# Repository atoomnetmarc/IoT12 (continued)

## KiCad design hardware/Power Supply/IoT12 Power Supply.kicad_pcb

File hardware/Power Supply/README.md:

This Power Supply PCB powers the IoT12 Control Board. It features a relay that can be activated by the Control Board to provide 24V power to the soldering iron. However, the relay can only be activated when the user switch on J2 is closed. This enables the user to power down the heating of the soldering iron independent of what the Control Board is able to, which is a nice feature of an internet connected soldering station.

# Warning

If you choose to replicate and use this PCB you are doing so on your own risk. It is very much possible to set your house on fire when something goes wrong or die when touching the wrong spots on the PCB.

When handling this PCB you are working with dangerous mains voltage ⚡. When touched it hurts the entire time you are dying ☠️. The bottom and top the PCB contain exposed tracks and screw terminals carry deadly mains voltage.

In conclusion, do not use this PCB.

# Assembly instructions Power Supply

Use the [interactive BOM](bom/ibom.html) to identify values and positions of the components.

Solder every SMD component. Begin with the smallest, end with the tallest.

Solder every through hole component. Begin with the smallest, end with the tallest However, do not solder the Mean Well power supply (PS1) module itself yet.

Clean the PCB.

You have now something that looks like this:

Connect current limited (100mA) 24V on the outputs of where PS1 should be. Possibly you could connect the right leg of F1 to 24V. Current should be under 10mA. Now D4 should light up. Measure the 5V pin, it should measure about 5.2V.
Connect a jumper to J2. Connect 3V3 to gnd and the '+24V ON'-pin of J3. D5 should light up and you hear a relay click. Current increases to about 20mA.

All went well? Disconnect 24V and solder PS1.

Measure 1M between GND on J3 and Earth on J1. Measure no connection between GND on J3 and L and N on J1.

Place bottom of PCB on isolating material.

Connect leads of an unconnected grounded mains cable to J1. Use the correct screw terminal for the correct mains line. If top of PCB is not clear enough, use labels on bottom of PCB and/or consult the PCB design files.

Connect multimeter to right leg of F1 and GND to measure voltage.

⚡ Connect the mains cable to the wall socket.

LED D4 should light up again. Look, no touch, at multimeter. It should read 24V.

Disconnect the mains cable from the wall socket. Disconnect multimeter. Notice D4 is still lit. It will stop emitting light after some unit of time. The capacitors in the Mean Well power supply still contain some charge and are discharging slowly.

# Done

Done!

# Pinout J1, high voltage side

AC power input.

| Pin # | Description                                       |
| ----- | ------------------------------------------------- |
| 1     | Earth, connected with 990KΩ resistor array to GND |
| 2     | AC line                                           |
| 3     | AC neutral                                        |

# Pinout J2, 24v interlock switch

In series with 24V_ON so the user can override when soldering iron heater receives power.

| Pin # | Description |
| ----- | ----------- |
| 1     | 24V_ON      |
| 2     | 24V_ON      |

# Pinout J3, Board-to-board

Goes to control board.

| Pin # | Description        |
| ----- | ------------------ |
| 1     | 24V switched power |
| 2     | 5V always on       |
| 3     | GND                |
| 4     | 24V_ON             |

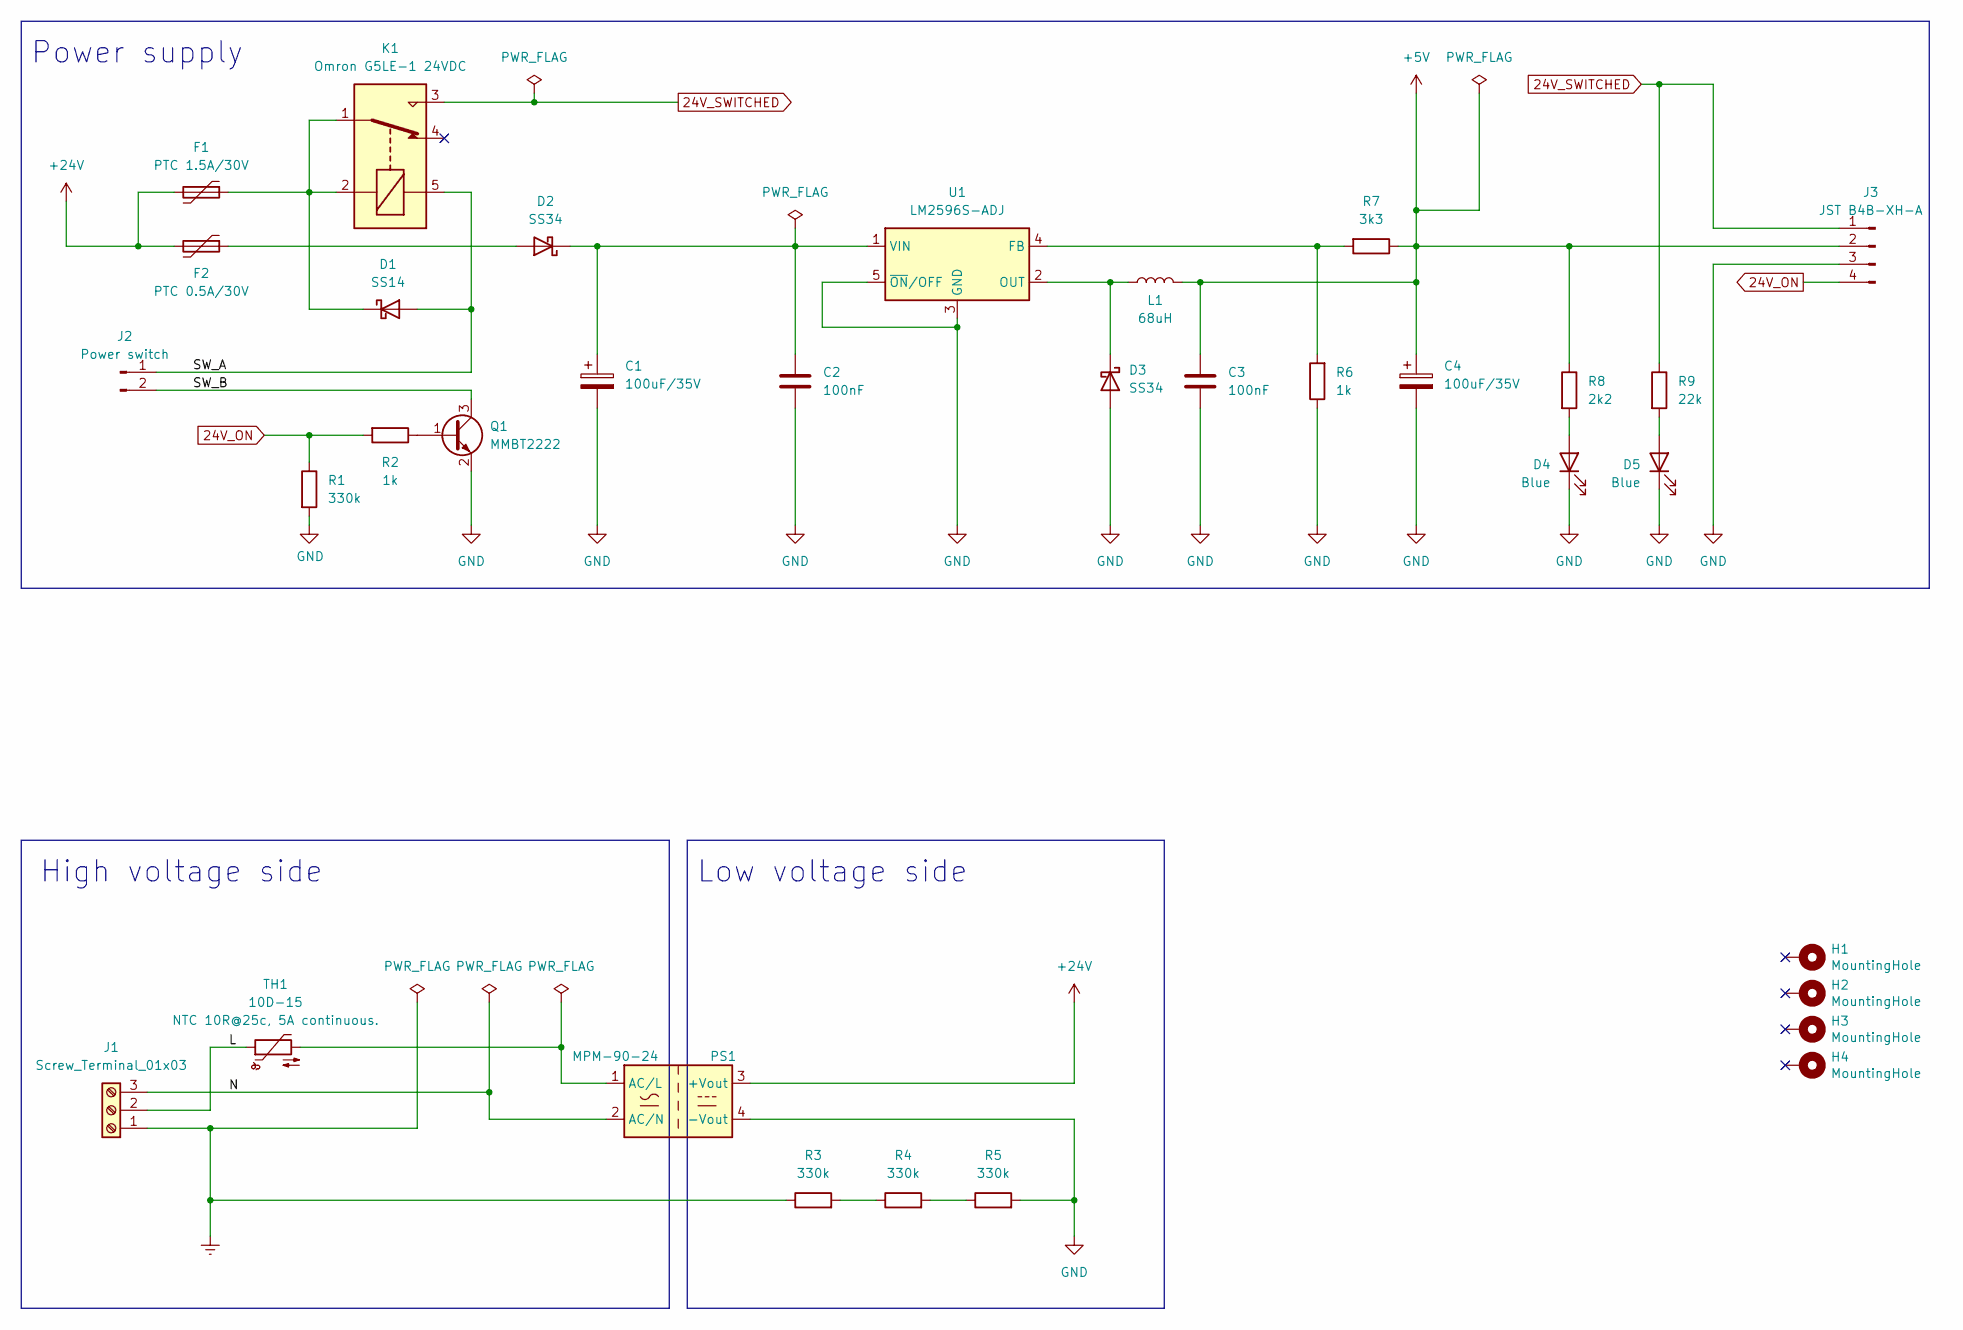
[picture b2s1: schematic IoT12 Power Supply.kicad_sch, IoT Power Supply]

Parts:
C1, C4: 100uF/35V; CP_Elec_6.3x7.7
C2, C3: 100nF; C_0805_2012Metric_Pad1.18x1.45mm_HandSolder
D1: SS14; D_SMA
D2, D3: SS34; D_SMA
D4, D5: Blue; LED_0805_2012Metric_Pad1.15x1.40mm_HandSolder
F1: PTC 1.5A/30V; RV_Disc_D9mm_W3.3mm_P5mm
F2: PTC 0.5A/30V; RV_Disc_D7mm_W3.4mm_P5mm
H1, H2, H3, H4: MountingHole; MountingHole_3.2mm_M3_Pad_Via
J1: Screw_Terminal_01x03; TerminalBlock_Weidmueller-PM-5.08-03-90-3.5SN-BK-BX
J2: JST B2B-XH-A; JST_XH_B2B-XH-A_1x02_P2.50mm_Vertical
J3: JST B4B-XH-A; JST_XH_B4B-XH-A_1x04_P2.50mm_Vertical
K1: Omron G5LE-1 24VDC; Relay_SPDT_Omron-G5LE-1
L1: 68uH; L_12x12mm_H8mm
PS1: MPM-90-24; Converter_ACDC_MeanWell_MPM-90-xx_THT
Q1: MMBT2222; SOT-23
R1, R3, R4, R5: 330k; R_0805_2012Metric_Pad1.20x1.40mm_HandSolder
R2, R6: 1k; R_0805_2012Metric_Pad1.20x1.40mm_HandSolder
R7: 3k3; R_0805_2012Metric_Pad1.20x1.40mm_HandSolder
R8: 2k2; R_0805_2012Metric_Pad1.20x1.40mm_HandSolder
R9: 22k; R_0805_2012Metric_Pad1.20x1.40mm_HandSolder
TH1: 10D-15; RV_Disc_D15.5mm_W4.5mm_P7.5mm
U1: LM2596S-ADJ; TO-263-5_TabPin3

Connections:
24V_ON: J3.4, R1.1, R2.2
24V_SWITCHED: J3.1, K1.3, R9.1
+5V: C3.1, C4.1, J3.2, L1.2, R7.1, R8.1
+24V: F1.2, F2.2, PS1.3 (+Vout)
/L: J1.2, TH1.1
/N: J1.3, PS1.2 (AC/N)
/SW_A: D1.2 (A), J2.1, K1.5
/SW_B: J2.2, Q1.3 (C)
Earth: J1.1, R3.1
GND: C1.2, C2.2, C3.2, C4.2, D3.2 (A), D4.1 (K), D5.1 (K), J3.3, PS1.4 (-Vout), Q1.2 (E), R1.2, R5.2, R6.1, U1.3 (GND), U1.5 (~ON/OFF)
unnamed: D1.1 (K), F1.1, K1.1, K1.2
unnamed: D2.2 (A), F2.1
unnamed: C1.1, C2.1, D2.1 (K), U1.1 (VIN)
unnamed: D3.1 (K), L1.1, U1.2 (OUT)
unnamed: D4.2 (A), R8.2
unnamed: D5.2 (A), R9.2
unnamed: PS1.1 (AC/L), TH1.2
unnamed: Q1.1 (B), R2.1
unnamed: R3.2, R4.1
unnamed: R4.2, R5.1
unnamed: R6.2, R7.2, U1.4 (FB)

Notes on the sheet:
Low voltage side
Power supply
High voltage side

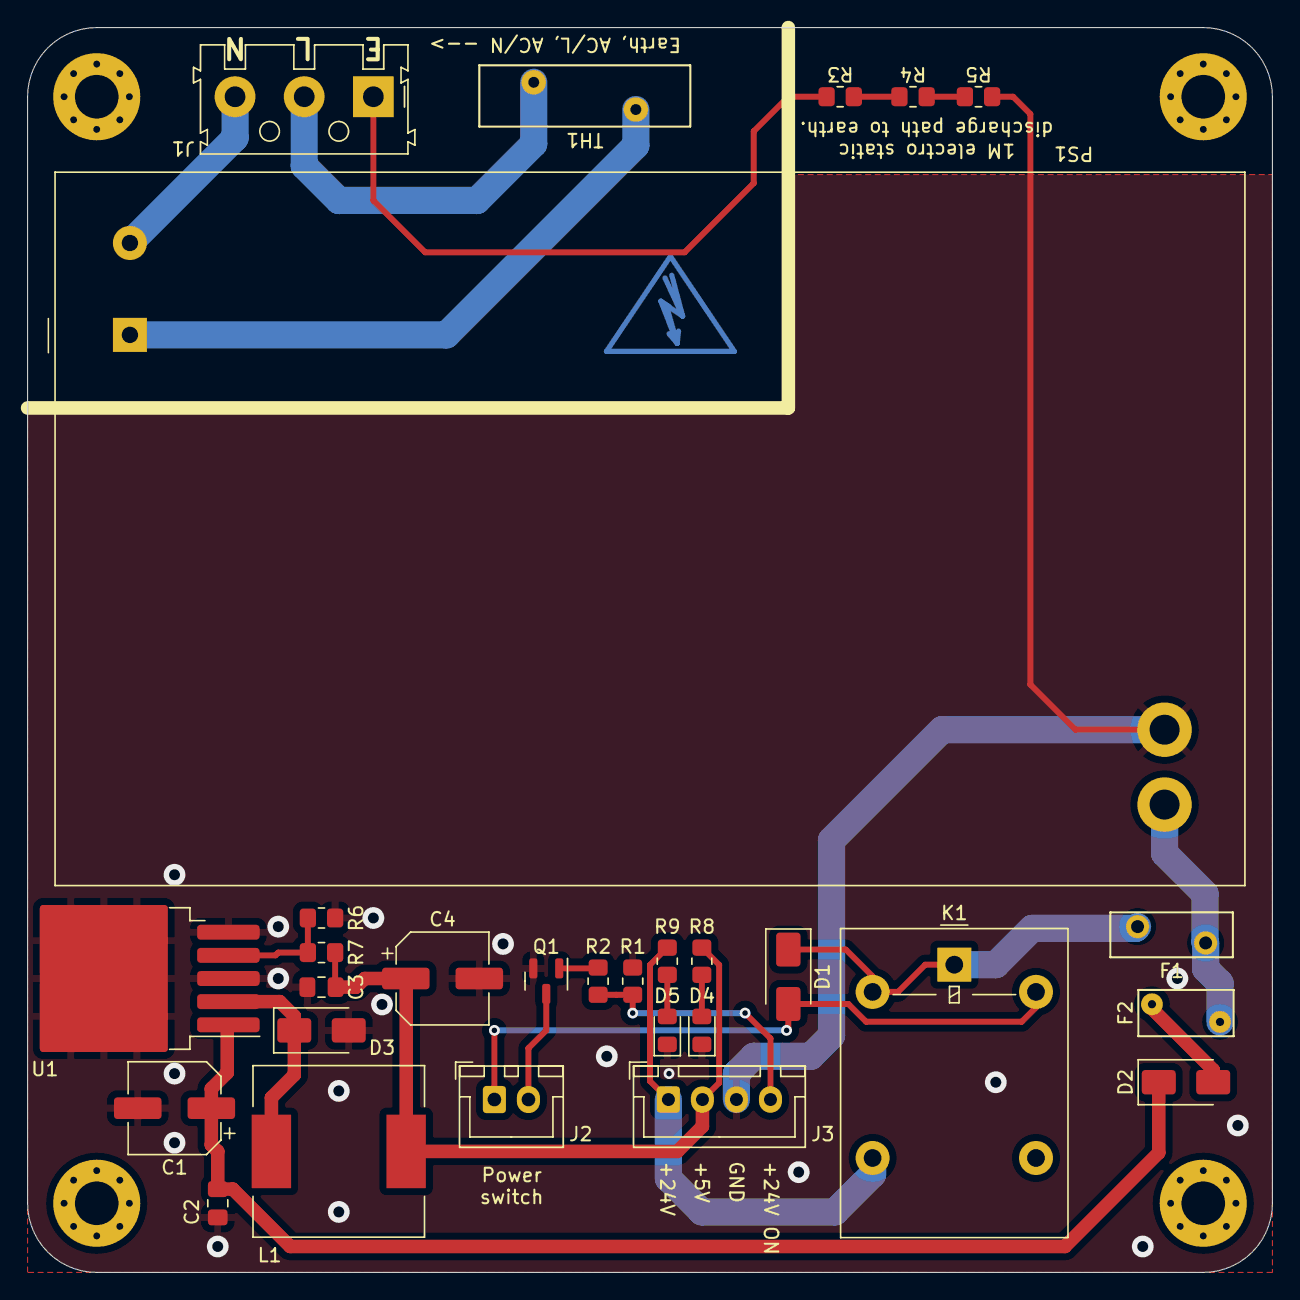
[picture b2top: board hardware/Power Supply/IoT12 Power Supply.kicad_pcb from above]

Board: 2 copper layers, 91.4 x 91.4 mm, 33 parts (0 on the bottom side), 21 nets.

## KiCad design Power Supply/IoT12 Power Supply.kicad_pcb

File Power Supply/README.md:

# Warning

If you choose to replicate and use this PCB you are doing so on your own risk. It is very much possible to set your house on fire when something goes wrong or die when touching the wrong spots on the PCB.

When handling this PCB you are working with dangerous mains voltage ⚡. When touched it hurts the entire time you are dying ☠️. The bottom and top the PCB contain exposed tracks and screw terminals carrying deadly mains voltage.

In conclusion, do not use this PCB. Power the IoT12 control board with some other safe and certified power supply.

# Assembly instructions Power Supply

## Solder

Solder components in the following order.
Use the [interactive BOM](bom/ibom.html) for values and positions of the components.

### Resistor

R2.

### Diode

D2.

### Screw terminal

J1, J2.

### Power supply

One off PS1, PS2 or PS3.

## Testing

Place bottom of PCB on isolating material.

Connect leads of a mains cable to J1. Use the correct screw terminal for the correct mains line. If top of PCB is not clear enough, use labels on bottom of PCB and/or consult the PCB design files.

⚡ Connect the mains cable to the wall socket.

Notice the green LED lighting up. Now carefully measure the low voltage side on screw terminal J2. You should measure 24V volts (if you mounted a Mean Well MPM-90-24).

Disconnect the mains cable from the wall socket. Notice that the green LED is still lit. It will stop emitting light after some unit of time. The capacitors in the Mean Well power supply still contain some chare and are discharging slowly.

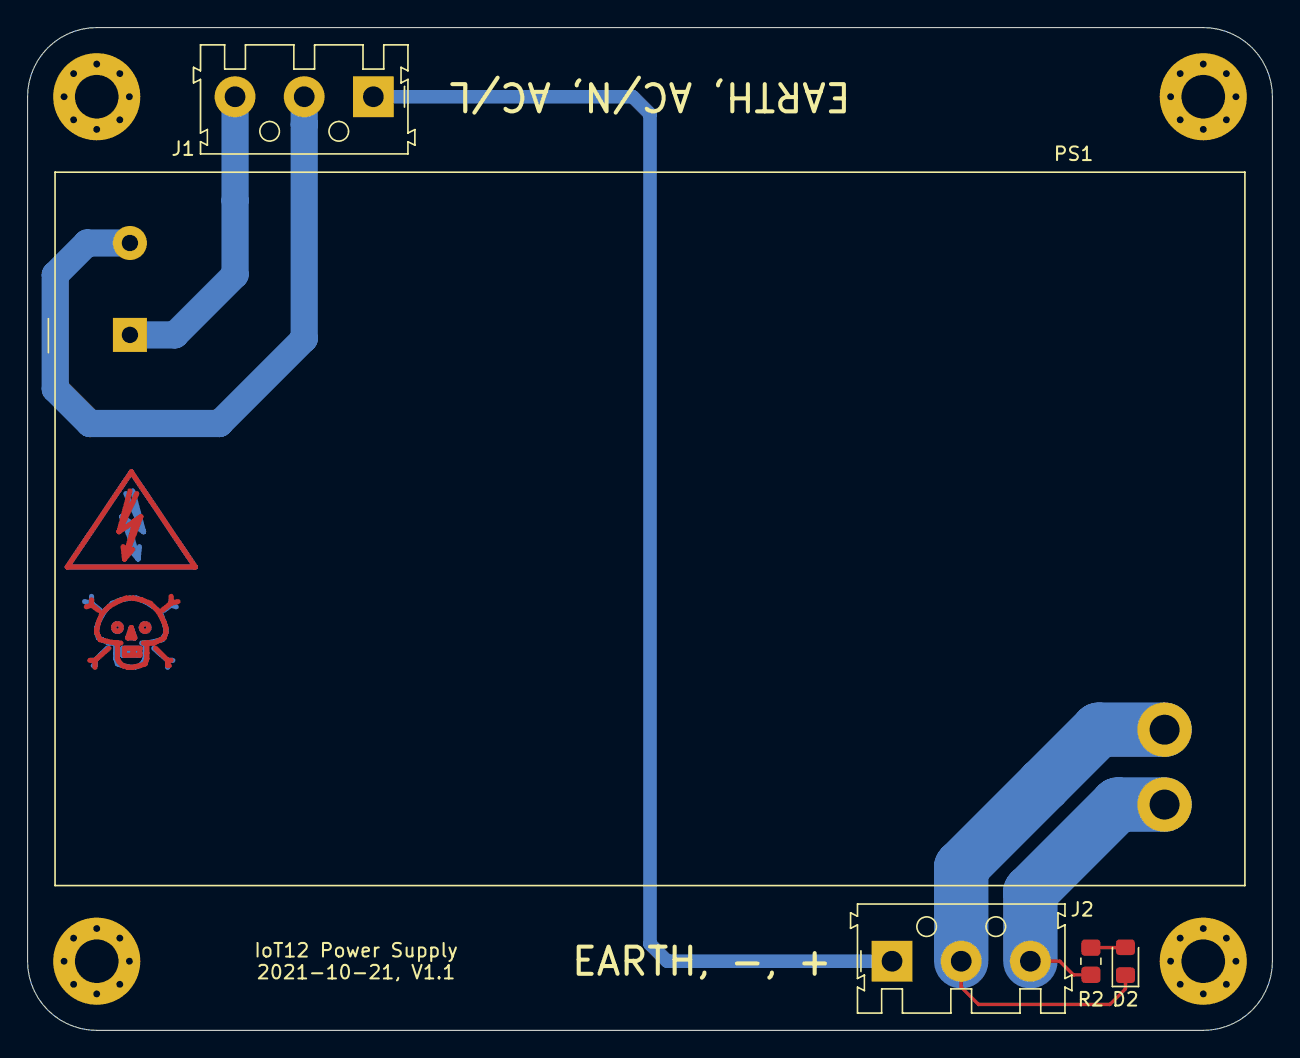
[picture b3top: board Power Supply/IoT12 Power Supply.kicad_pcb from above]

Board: 2 copper layers, 91.4 x 73.7 mm, 9 parts (0 on the bottom side), 6 nets.

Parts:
D2: Green; LED_0805_2012Metric_Pad1.15x1.40mm_HandSolder
H1, H2, H3, H4: MountingHole; MountingHole_3.2mm_M3_Pad_Via
J1, J2: Screw_Terminal_01x03; TerminalBlock_Weidmueller-PM-5.08-03-90-3.5SN-BK-BX
PS1: MPM-90-24; Converter_ACDC_MeanWell_MPM-90-xx_THT
R2: 4K7; R_0805_2012Metric_Pad1.20x1.40mm_HandSolder

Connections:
/L: J1.3, PS1.1
/N: J1.2, PS1.2
/Vout+: J2.3, PS1.3, R2.1
/Vout-: D2.1, J2.2, PS1.4
Earth: J1.1, J2.1
unnamed: D2.2, R2.2

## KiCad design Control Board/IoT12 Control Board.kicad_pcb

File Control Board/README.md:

# Assembly instructions Control Board

## Solder

Solder components in the following order.
Use the [interactive BOM](bom/ibom.html) for values and positions of the components.

### Integrated circuit

U1.
U2.
U3, U4.
U5.
U6.
U7.

### Transistor

Q1, Q2.
Q3.

### Diode

D1, D2, D3, D4, D12.
D5.
D6, D7, D8.
D9.
D10.
D11.

### Inductor

L1.
L2.

### Resistor

R1.
R10, R11, R12.
R20.
R21.
R30.
R31, R32, R33, R34.
R40.
R52.
R50, R51, R53, R54, R55, R56, R57, R58, R59, R82.
R60, R61, R62, R63. **Read schematic notes about these resistors.**
R64.
R70.
R71, R72.
R80, R81, R83, R84.

### Capacitor

C1, C2.
C10.
C20, C21, C22.
C30, C31, C32, C33, C34, C35, C36, C37, C38.
C40, C41.
C50, C60, C61.
C70, C71, C73.

### Crystal

Y1.

## Clean PCB

[Clean your printed circuit board](http://letmegooglethat.com/?q=how+to+clean+flux+after+soldering). It should be squeaky clean, no flux residue or other crud should remain.

### Switch, back of PCB

SW2.

### Connector, back of PCB

J10.

### Connector, front of PCB

A2: 2 pcs of 1x8pin 2.54mm female headers.

### Connector, back of PCB

A1: 2 pcs of 1x19pin 2.54mm female headers.
J9, J10. 2x5pin 2.54mm male headers.

### Fuse, back of PCB

## Clean PCB, again.

Yes, do it.

### Encoder, front of PCB

Solder SW1 and remove nut and washer.

### Module, front of PCB

A3. Use pin male headers. Also for SPK pins.

## Inspect

Inspect all solder joints. They should all be [nicely soldered](https://www.google.com/search?q=proper+solder+joint), no [solder bridges](https://www.google.com/search?q=picture+of+a+solder+bridge) should be present. Have a magnifying glass or (digital) microscope? Use it.

### GX12-5 connector

Solder some wires between a GX12-5 socket connector and the back of the pcb. On the back of the pcb there are a few pads labeled 1 to 5, solder them to pin 1 to 5 on the GX12-5 connector.

| Pin#  | Wire color    | Description   |
| --:   | --            | --            |
| 1     | blue          | shake         |
| 2     | white         | NTC           |
| 3     | green         | ESD           |
| 4     | black         | T12-          |
| 5     | red           | T12+          |

## Testing

Connect a (KSGER) T12 solder iron handle with the T12 tip firmly seated inside.

- Measure about 1MΩ between the tip of the iron and EARTH hole at the Power supply connection on the PCB.
- Now measure some values at the solder iron connector holes.\
The heater resistor between 4 (black) and 5 (red): 8Ω
- Switch over to measure mV. When you have not touched the handle and tip for half an hour you should read 0mV. Grab the tip with your hand. You should notice an increasing voltage, possibly a rise until 0.1mV. It is possible your voltmeter is not capable of measuring in the microvolt range. You can heat the tip with a flame for a few seconds to increase the voltage some more.
- The NTC between 4 (black) and 2 (white): 5KΩ@22°C, but that could vary slightly when not measuring at the same room temperature.
- Test the tilt sensor. Point iron up and measure between 1 (blue) and 3 (green): >2MΩ\
Point iron down and measure a low resistance: <100Ω

Solder a red wire to 24V and black wire to GND of the power supply connector holes, both on the back.\
Slowly increase power supply until 10V with max 50mA power. Measure voltage at C71. You should measure 5V. The current draw should be under 10mA.

Switch off power supply and mount the LCD display module and the ESP32 module.

Increase maximum power supply current to 250mA. Instantly increase voltage to 5V, the slowly to 10V, current should not exceed 150mA. When at 10V the current draw should be under 100mA.
You may increase voltage to 24V, consumed power should be under 40mA.

When all tests went well, start writing your own firmware. Or [flash my firmware](https://github.com/atoomnetmarc/IoT12-firmware)

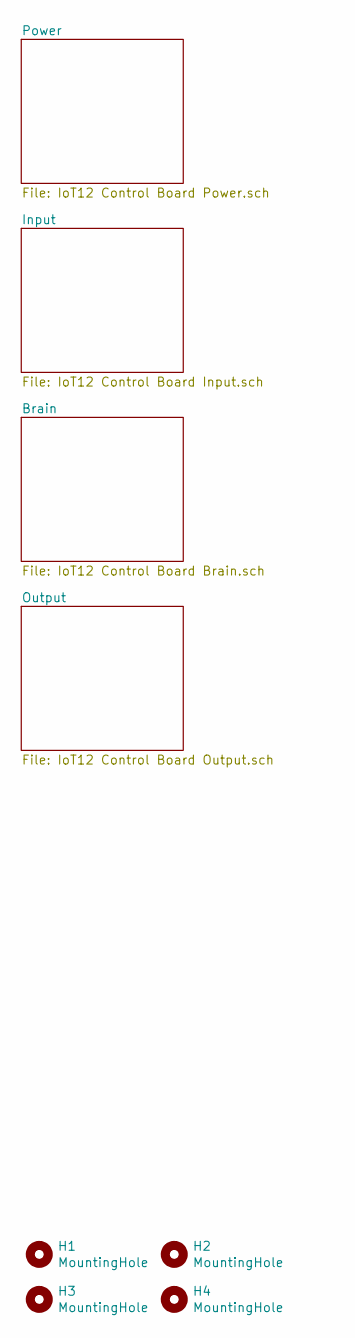
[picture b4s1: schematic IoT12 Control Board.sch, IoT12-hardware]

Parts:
H1, H2, H3, H4: MountingHole; MountingHole_3.2mm_M3_Pad_Via

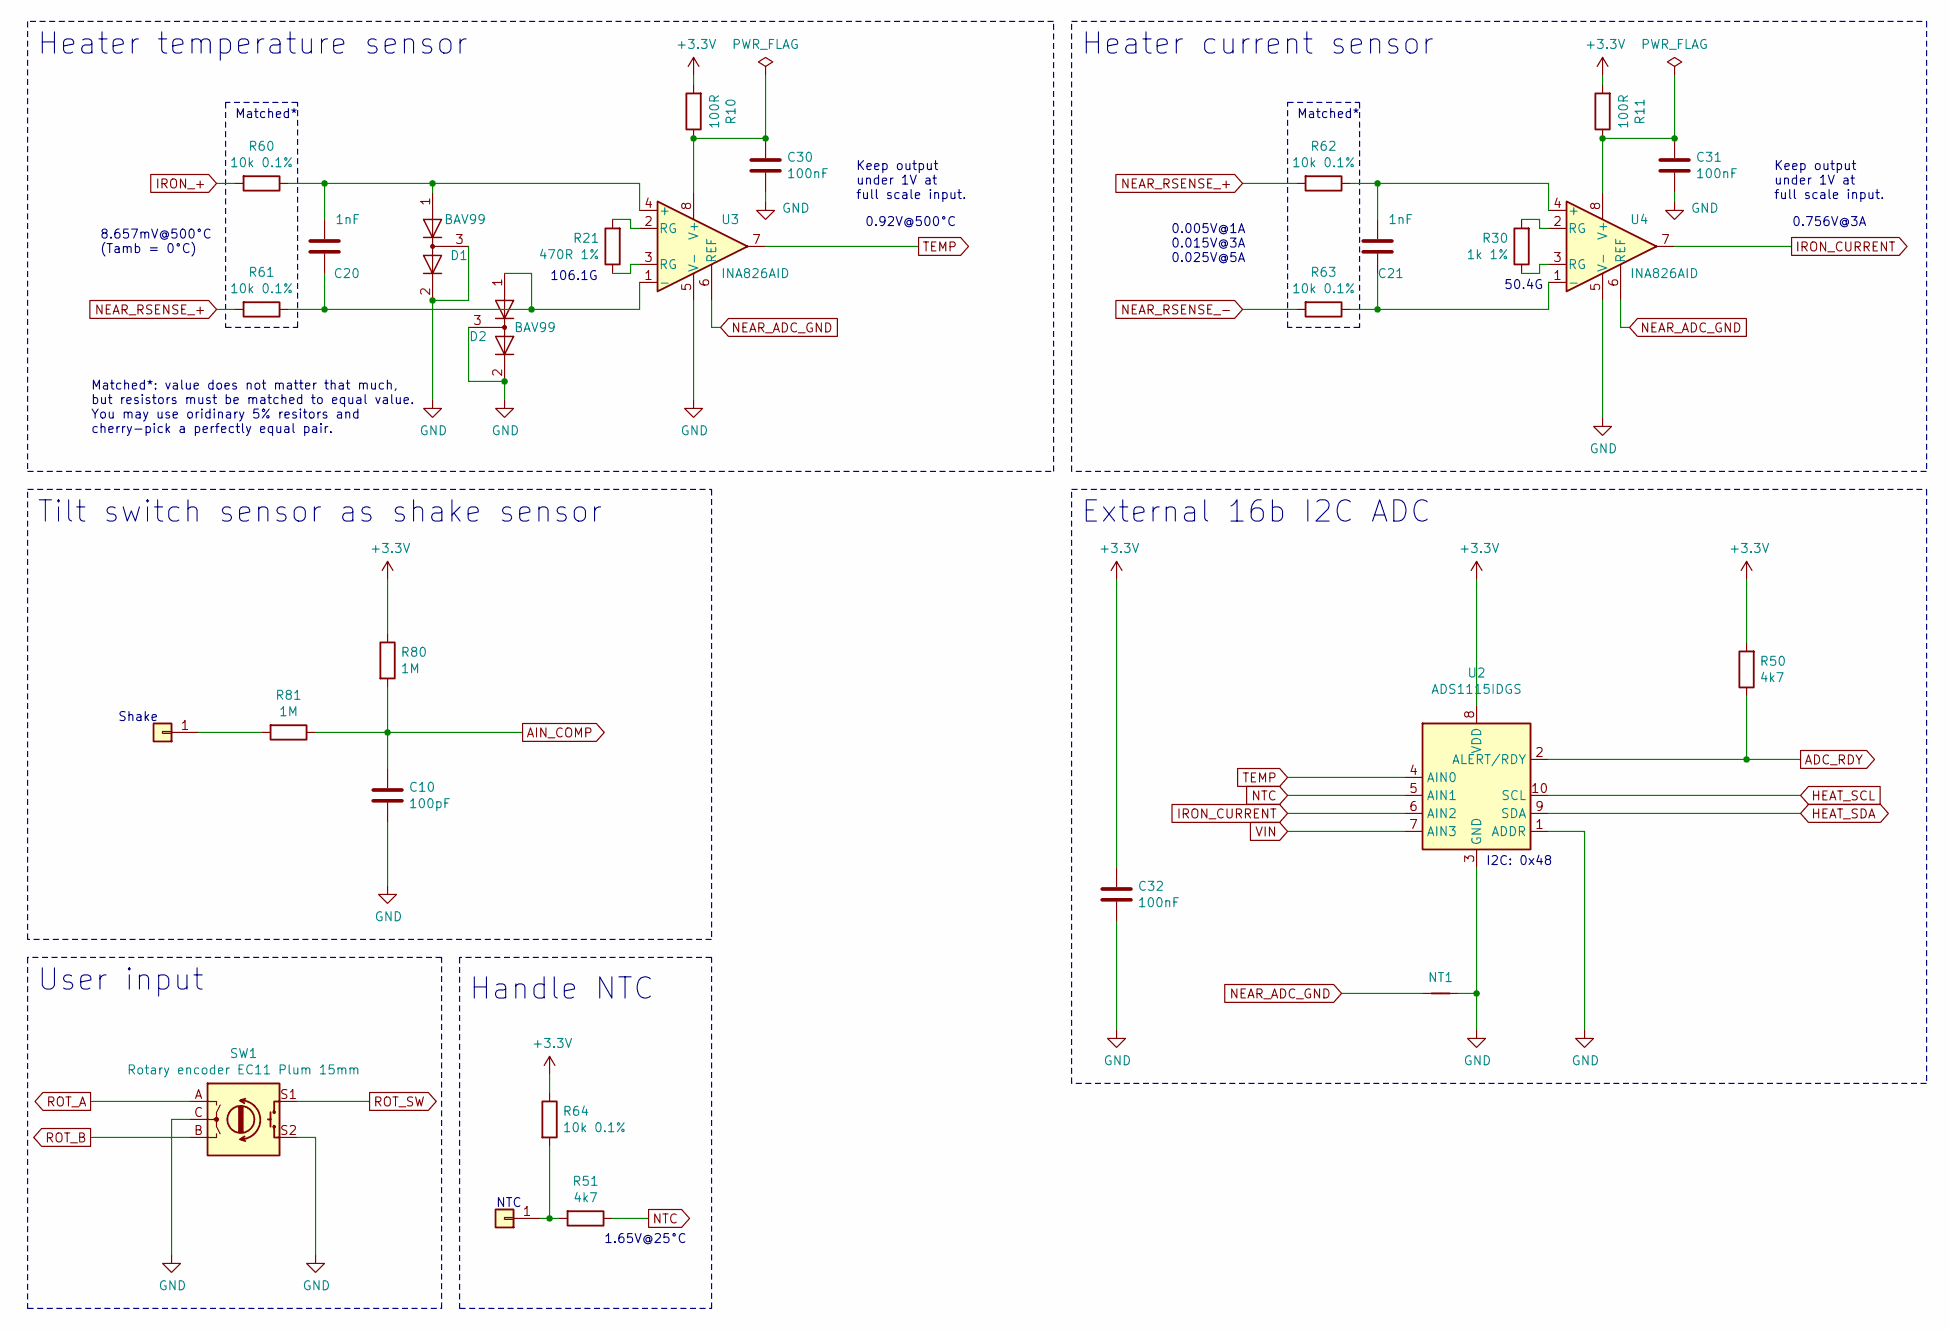
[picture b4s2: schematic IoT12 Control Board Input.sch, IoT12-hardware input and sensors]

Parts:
C10: 100pF; C_0805_2012Metric_Pad1.18x1.45mm_HandSolder
C20, C21: 1nF; C_0805_2012Metric_Pad1.18x1.45mm_HandSolder
C30, C31, C32: 100nF; C_0805_2012Metric_Pad1.18x1.45mm_HandSolder
D1, D2: BAV99; SOT-23
J1, J2: TestPoint_THTPad_D2.0mm_Drill1.0mm
NT1: NetTie-2_SMD_Pad0.25mm
R10, R11: 100R; R_0805_2012Metric_Pad1.20x1.40mm_HandSolder
R21: 470R 1%; R_0805_2012Metric_Pad1.20x1.40mm_HandSolder
R30: 1k 1%; R_0805_2012Metric_Pad1.20x1.40mm_HandSolder
R50, R51: 4k7; R_0805_2012Metric_Pad1.20x1.40mm_HandSolder
R60, R61, R62, R63, R64: 10k 0.1%; R_0805_2012Metric_Pad1.20x1.40mm_HandSolder
R80, R81: 1M; R_0805_2012Metric_Pad1.20x1.40mm_HandSolder
SW1: Rotary encoder EC11 Plum 15mm; RotaryEncoder_Alps_EC11E-Switch_Vertical_H20mm_CircularMoun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
U2: ADS1115IDGS; TSSOP-10_3x3mm_P0.5mm
U3, U4: INA826AID; SOIC-8_3.9x4.9mm_P1.27mm

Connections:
ADC_RDY: R50.1, U2.2 (ALERT/RDY); also elsewhere on the board
AIN_COMP: C10.1, R80.2, R81.1; also elsewhere on the board
GND: C10.2, C30.2, C31.2, C32.2, D1.2 (A), D1.3 (K), D2.2 (A), D2.3 (K), NT1.2, SW1.C, SW1.S2, U2.1 (ADDR), U2.3 (GND), U3.5 (V-), U4.5 (V-); also elsewhere on the board
HEAT_SCL: U2.10 (SCL); also elsewhere on the board
HEAT_SDA: U2.9 (SDA); also elsewhere on the board
IRON_+: R60.2; also elsewhere on the board
IRON_CURRENT: U2.6 (AIN2), U4.7; also elsewhere on the board
NEAR_ADC_GND: NT1.1, U3.6 (REF), U4.6 (REF)
NEAR_RSENSE_+: R61.2, R62.2; also elsewhere on the board
NEAR_RSENSE_-: R63.2; also elsewhere on the board
NTC: R51.1, U2.5 (AIN1); also elsewhere on the board
unnamed: C20.1, D1.1 (K), R60.1, U3.4 (+)
unnamed: C20.2, D2.1 (K), R61.1, U3.1 (-)
unnamed: C21.1, R62.1, U4.4 (+)
unnamed: C21.2, R63.1, U4.1 (-)
unnamed: C30.1, R10.1, U3.8 (V+)
unnamed: C31.1, R11.1, U4.8 (V+)
unnamed: J1.1, R81.2
unnamed: J2.1, R51.2, R64.2
unnamed: R21.1, U3.3 (RG)
unnamed: R21.2, U3.2 (RG)
unnamed: R30.1, U4.3 (RG)
unnamed: R30.2, U4.2 (RG)
ROT_A: SW1.A; also elsewhere on the board
ROT_B: SW1.B; also elsewhere on the board
ROT_SW: SW1.S1; also elsewhere on the board
TEMP: U2.4 (AIN0), U3.7; also elsewhere on the board
VIN: U2.7 (AIN3); also elsewhere on the board

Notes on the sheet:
User input
Heater temperature sensor
Heater current sensor
Handle NTC
NTC
Shake
Tilt switch sensor as shake sensor
50.4G
Matched*
0.005V@1A 0.015V@3A 0.025V@5A
106.1G
8.657mV@500°C (Tamb = 0°C)
0.92V@500°C
1.65V@25°C
Matched*: value does not matter that much, but resistors must be matched to equal value. You may use oridinary 5% resitors and cherry-pick a perfectly equal pair.
Keep output under 1V at full scale input.
0.756V@3A
External 16b I2C ADC
I2C: 0x48

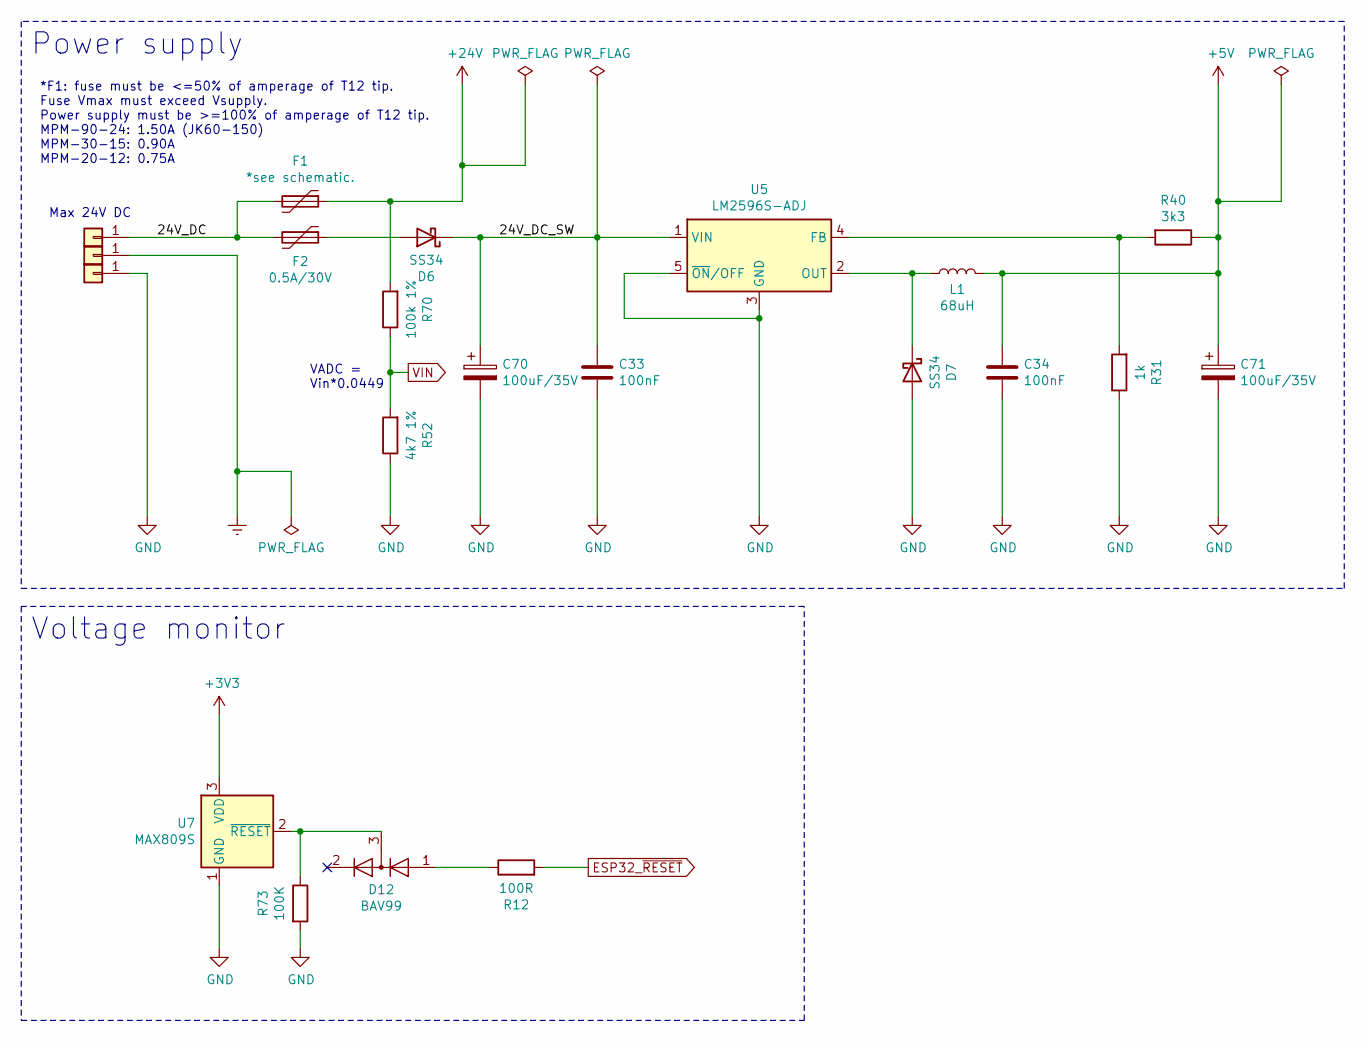
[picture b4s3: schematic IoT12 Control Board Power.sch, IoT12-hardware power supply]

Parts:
C33, C34: 100nF; C_0805_2012Metric_Pad1.18x1.45mm_HandSolder
C70, C71: 100uF/35V; CP_Elec_6.3x7.7
D6, D7: SS34; D_SMA
D12: BAV99; SOT-23
F1: *see schematic.; Fuse_Bourns_MF-RG1000
F2: 0.5A/30V; Fuse_Bourns_MF-RG400
J6, J7, J8: TestPoint_THTPad_D2.0mm_Drill1.0mm
L1: 68uH; L_12x12mm_H8mm
R12: 100R; R_0805_2012Metric_Pad1.20x1.40mm_HandSolder
R31: 1k; R_0805_2012Metric_Pad1.20x1.40mm_HandSolder
R40: 3k3; R_0805_2012Metric_Pad1.20x1.40mm_HandSolder
R52: 4k7 1%; R_0805_2012Metric_Pad1.20x1.40mm_HandSolder
R70: 100k 1%; R_0805_2012Metric_Pad1.20x1.40mm_HandSolder
R73: 100K; R_0805_2012Metric_Pad1.20x1.40mm_HandSolder
U5: LM2596S-ADJ; TO-263-5_TabPin3
U7: MAX809S; SOT-23

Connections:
+5V: C34.1, C71.1, L1.2, R40.1; also elsewhere on the board
+24V: F1.1, R70.2; also elsewhere on the board
/Power/24V_DC: F1.2, F2.2, J6.1
/Power/24V_DC_SW: C33.1, C70.1, D6.1 (K), U5.1 (VIN)
ESP32_~RESET: R12.2; also elsewhere on the board
Earth: J7.1; also elsewhere on the board
GND: C33.2, C34.2, C70.2, C71.2, D7.2 (A), J8.1, R31.1, R52.1, R73.2, U5.3 (GND), U5.5 (~ON~/OFF), U7.1 (GND); also elsewhere on the board
unnamed: D6.2 (A), F2.1
unnamed: D7.1 (K), L1.1, U5.2 (OUT)
unnamed: D12.1 (K), R12.1
unnamed: D12.3 (K), R73.1, U7.2 (~RESET)
unnamed: R31.2, R40.2, U5.4 (FB)
VIN: R52.2, R70.1; also elsewhere on the board

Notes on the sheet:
Power supply
VADC = Vin*0.0449
Max 24V DC
Voltage monitor
*F1: fuse must be <=50% of amperage of T12 tip. Fuse Vmax must exceed Vsupply. Power supply must be >=100% of amperage of T12 tip. MPM-90-24: 1.50A (JK60-150) MPM-30-15: 0.90A MPM-20-12: 0.75A

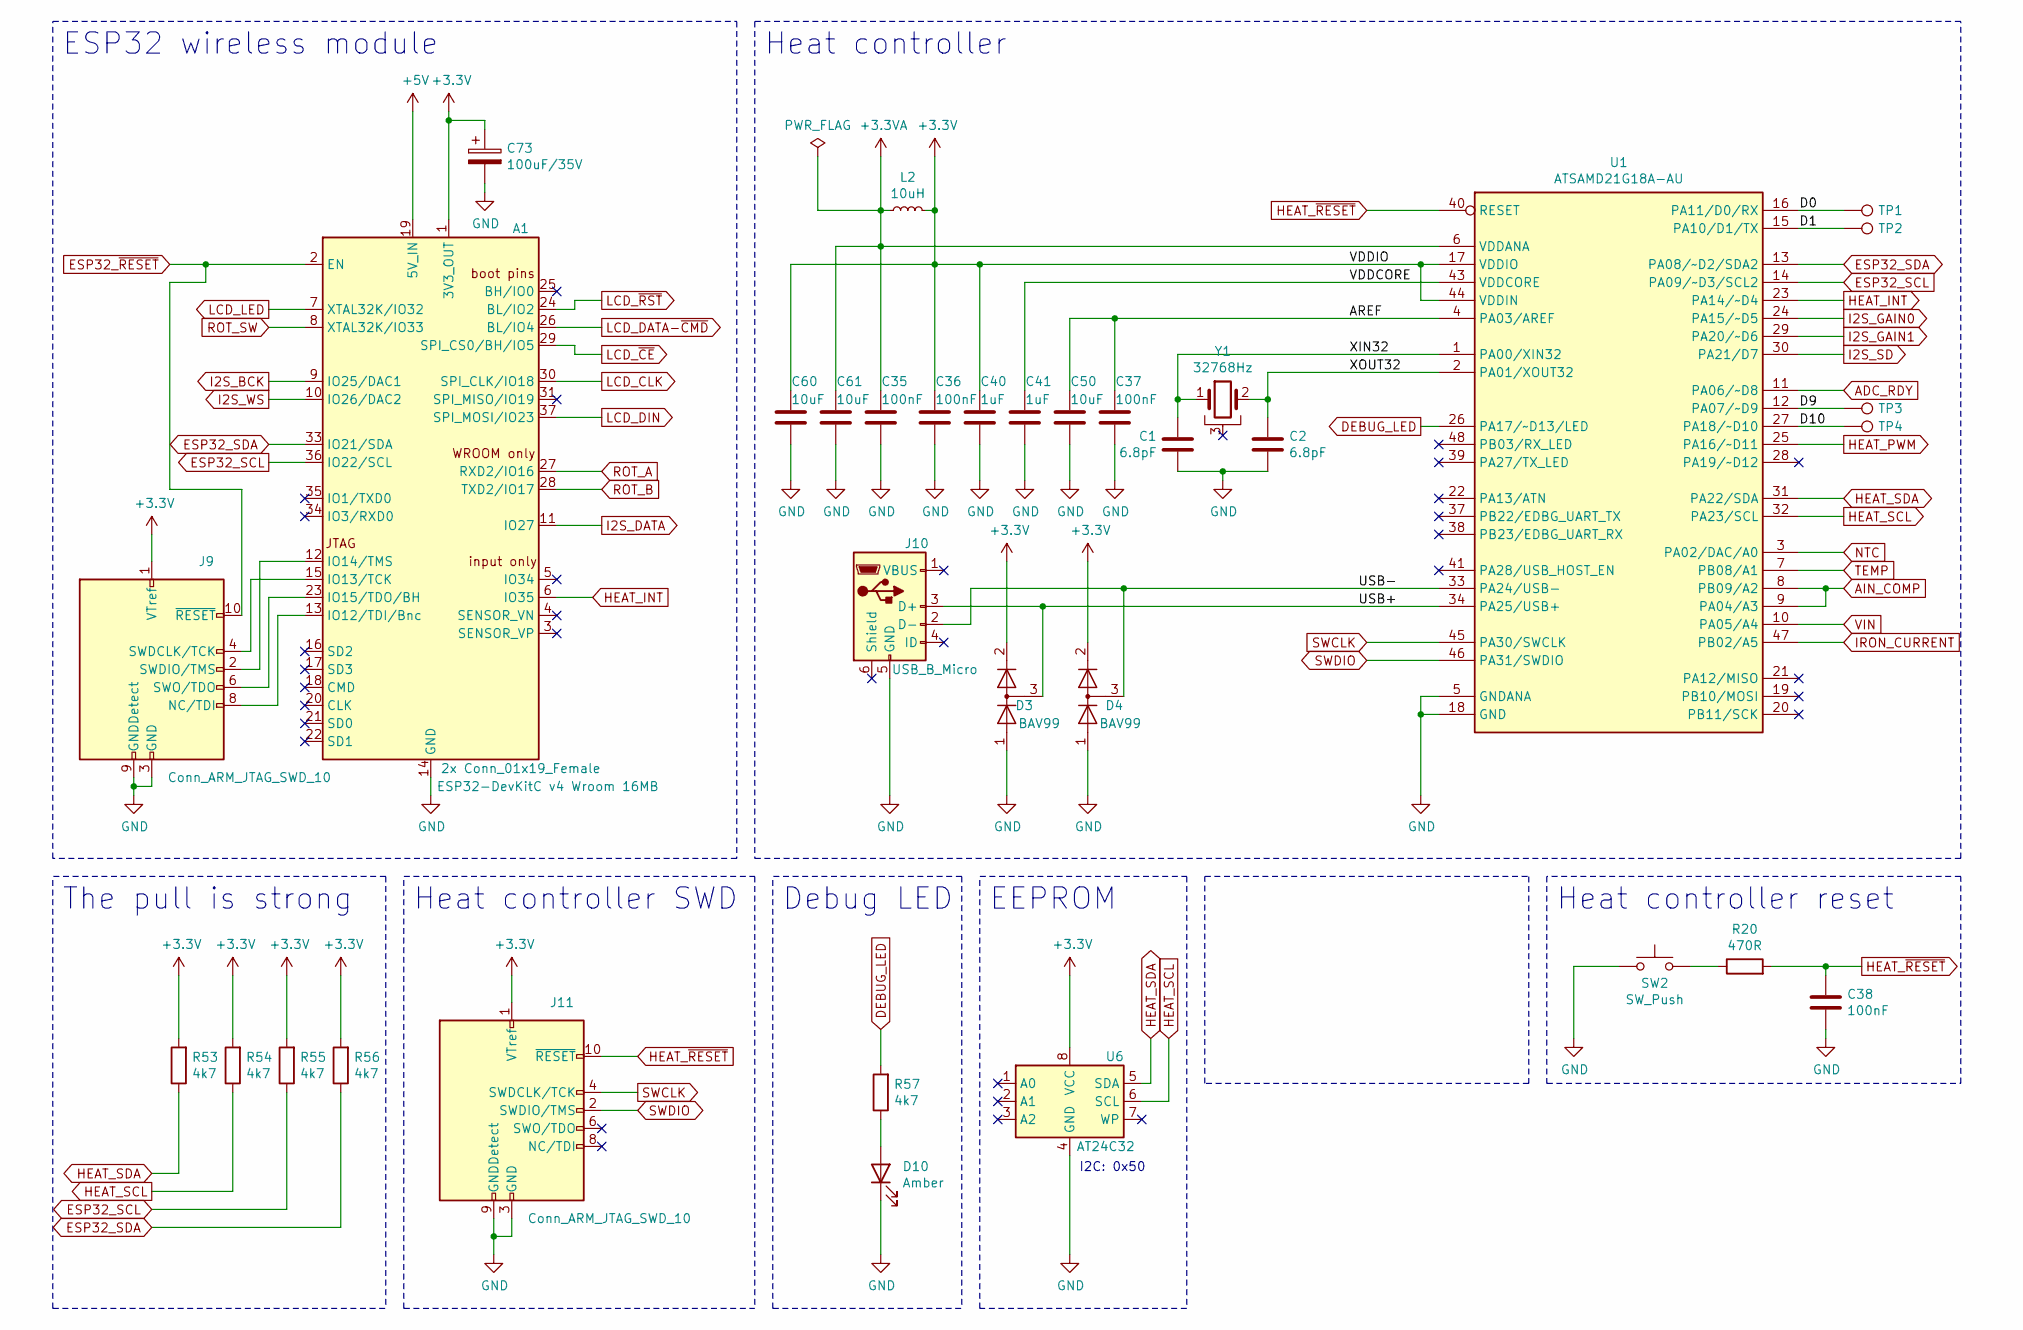
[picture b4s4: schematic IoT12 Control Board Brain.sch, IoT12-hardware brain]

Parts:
A1: 2x Conn_01x19_Female; ESP32-DevKitC
C1, C2: 6.8pF; C_0805_2012Metric_Pad1.18x1.45mm_HandSolder
C35, C36, C37, C38: 100nF; C_0805_2012Metric_Pad1.18x1.45mm_HandSolder
C40, C41: 1uF; C_0805_2012Metric_Pad1.18x1.45mm_HandSolder
C50, C60, C61: 10uF; C_0805_2012Metric_Pad1.18x1.45mm_HandSolder
C73: 100uF/35V; CP_Elec_6.3x7.7
D3, D4: BAV99; SOT-23
D10: Amber; LED_0805_2012Metric_Pad1.15x1.40mm_HandSolder
J9, J11: Conn_ARM_JTAG_SWD_10; PinHeader_2x05_P2.54mm_Vertical
J10: USB_B_Micro; USB_Micro-B_Amphenol_10118194_Horizontal
L2: 10uH; L_0805_2012Metric_Pad1.15x1.40mm_HandSolder
R20: 470R; R_0805_2012Metric_Pad1.20x1.40mm_HandSolder
R53, R54, R55, R56, R57: 4k7; R_0805_2012Metric_Pad1.20x1.40mm_HandSolder
SW2: SW_Push; SW_SPST_CK_RS282G05A3
TP1, TP2, TP3, TP4: TestPoint; TestPoint_Pad_D0.75mm
U1: ATSAMD21G18A-AU; TQFP-48_7x7mm_P0.5mm
U6: AT24C32; SOIC-8_3.9x4.9mm_P1.27mm
Y1: 32768Hz; Crystal_C26-LF_D2.1mm_L6.5mm_Horizontal_1EP_style1

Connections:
+3.3VA: C35.1, C61.1, L2.1, U1.6 (VDDANA)
+5V: A1.19 (5V_IN); also elsewhere on the board
/Brain/AREF: C37.1, C50.1, U1.4 (PA03/AREF)
/Brain/D0: TP1.1, U1.16 (PA11/D0/RX)
/Brain/D1: TP2.1, U1.15 (PA10/D1/TX)
/Brain/D9: TP3.1, U1.12 (PA07/~~D9)
/Brain/D10: TP4.1, U1.27 (PA18/~~D10)
/Brain/USB+: D3.3 (K), J10.3 (D+), U1.34 (PA25/USB+)
/Brain/USB-: D4.3 (K), J10.2 (D-), U1.33 (PA24/USB-)
/Brain/VDDCORE: C41.1, U1.43 (VDDCORE)
/Brain/XIN32: C1.1, U1.1 (PA00/XIN32), Y1.1
/Brain/XOUT32: C2.1, U1.2 (PA01/XOUT32), Y1.2
ADC_RDY: U1.11 (PA06/~~D8); also elsewhere on the board
AIN_COMP: U1.8 (PB09/A2), U1.9 (PA04/A3); also elsewhere on the board
DEBUG_LED: R57.2, U1.26 (PA17/~~D13/LED)
ESP32_SCL: A1.36 (IO22/SCL), R55.1, U1.14 (PA09/~~D3/SCL2)
ESP32_SDA: A1.33 (IO21/SDA), R56.1, U1.13 (PA08/~~D2/SDA2)
ESP32_~RESET: A1.2 (EN), J9.10 (~RESET~); also elsewhere on the board
GND: A1.14 (GND), A1.32 (GND), A1.38 (GND), C1.2, C2.2, C35.2, C36.2, C37.2, C38.2, C40.2, C41.2, C50.2, C60.2, C61.2, C73.2, D3.1 (K), D4.1 (K), D10.1 (K), J9.3 (GND), J9.5 (GND), J9.9 (GNDDetect), J10.5 (GND), J11.3 (GND), J11.5 (GND), J11.9 (GNDDetect), SW2.1, U1.5 (GNDANA), U1.18 (GND), U1.35 (GND), U1.42 (GND), U6.4 (GND); also elsewhere on the board
HEAT_INT: A1.6 (IO35), U1.23 (PA14/~~D4)
HEAT_PWM: U1.25 (PA16/~~D11); also elsewhere on the board
HEAT_SCL: R54.1, U1.32 (PA23/SCL), U6.6 (SCL); also elsewhere on the board
HEAT_SDA: R53.1, U1.31 (PA22/SDA), U6.5 (SDA); also elsewhere on the board
HEAT_~RESET: C38.1, J11.10 (~RESET~), R20.2, U1.40 (RESET)
I2S_BCK: A1.9 (IO25/DAC1); also elsewhere on the board
I2S_DATA: A1.11 (IO27); also elsewhere on the board
I2S_GAIN0: U1.24 (PA15/~~D5); also elsewhere on the board
I2S_GAIN1: U1.29 (PA20/~~D6); also elsewhere on the board
I2S_SD: U1.30 (PA21/D7); also elsewhere on the board
I2S_WS: A1.10 (IO26/DAC2); also elsewhere on the board
IRON_CURRENT: U1.47 (PB02/A5); also elsewhere on the board
LCD_CLK: A1.30 (SPI_CLK/IO18); also elsewhere on the board
LCD_DATA-~CMD: A1.26 (BL/IO4); also elsewhere on the board
LCD_DIN: A1.37 (SPI_MOSI/IO23); also elsewhere on the board
LCD_LED: A1.7 (XTAL32K/IO32); also elsewhere on the board
LCD_~CE: A1.29 (SPI_CS0/BH/IO5); also elsewhere on the board
LCD_~RST: A1.24 (BL/IO2); also elsewhere on the board
NTC: U1.3 (PA02/DAC/A0); also elsewhere on the board
unnamed: A1.12 (IO14/TMS), J9.2 (SWDIO/TMS)
unnamed: A1.13 (IO12/TDI/Bnc), J9.8 (NC/TDI)
unnamed: A1.15 (IO13/TCK), J9.4 (SWDCLK/TCK)
unnamed: A1.23 (IO15/TDO/BH), J9.6 (SWO/TDO)
unnamed: D10.2 (A), R57.1
unnamed: R20.1, SW2.2
ROT_A: A1.27 (RXD2/IO16); also elsewhere on the board
ROT_B: A1.28 (TXD2/IO17); also elsewhere on the board
ROT_SW: A1.8 (XTAL32K/IO33); also elsewhere on the board
SWCLK: J11.4 (SWDCLK/TCK), U1.45 (PA30/SWCLK)
SWDIO: J11.2 (SWDIO/TMS), U1.46 (PA31/SWDIO)
TEMP: U1.7 (PB08/A1); also elsewhere on the board
VIN: U1.10 (PA05/A4); also elsewhere on the board

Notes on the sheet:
ESP32 wireless module
Heat controller
Heat controller SWD
Heat controller reset
Debug LED
The pull is strong
EEPROM
I2C: 0x50
